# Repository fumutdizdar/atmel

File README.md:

# atmel
Atmel328P için temel board

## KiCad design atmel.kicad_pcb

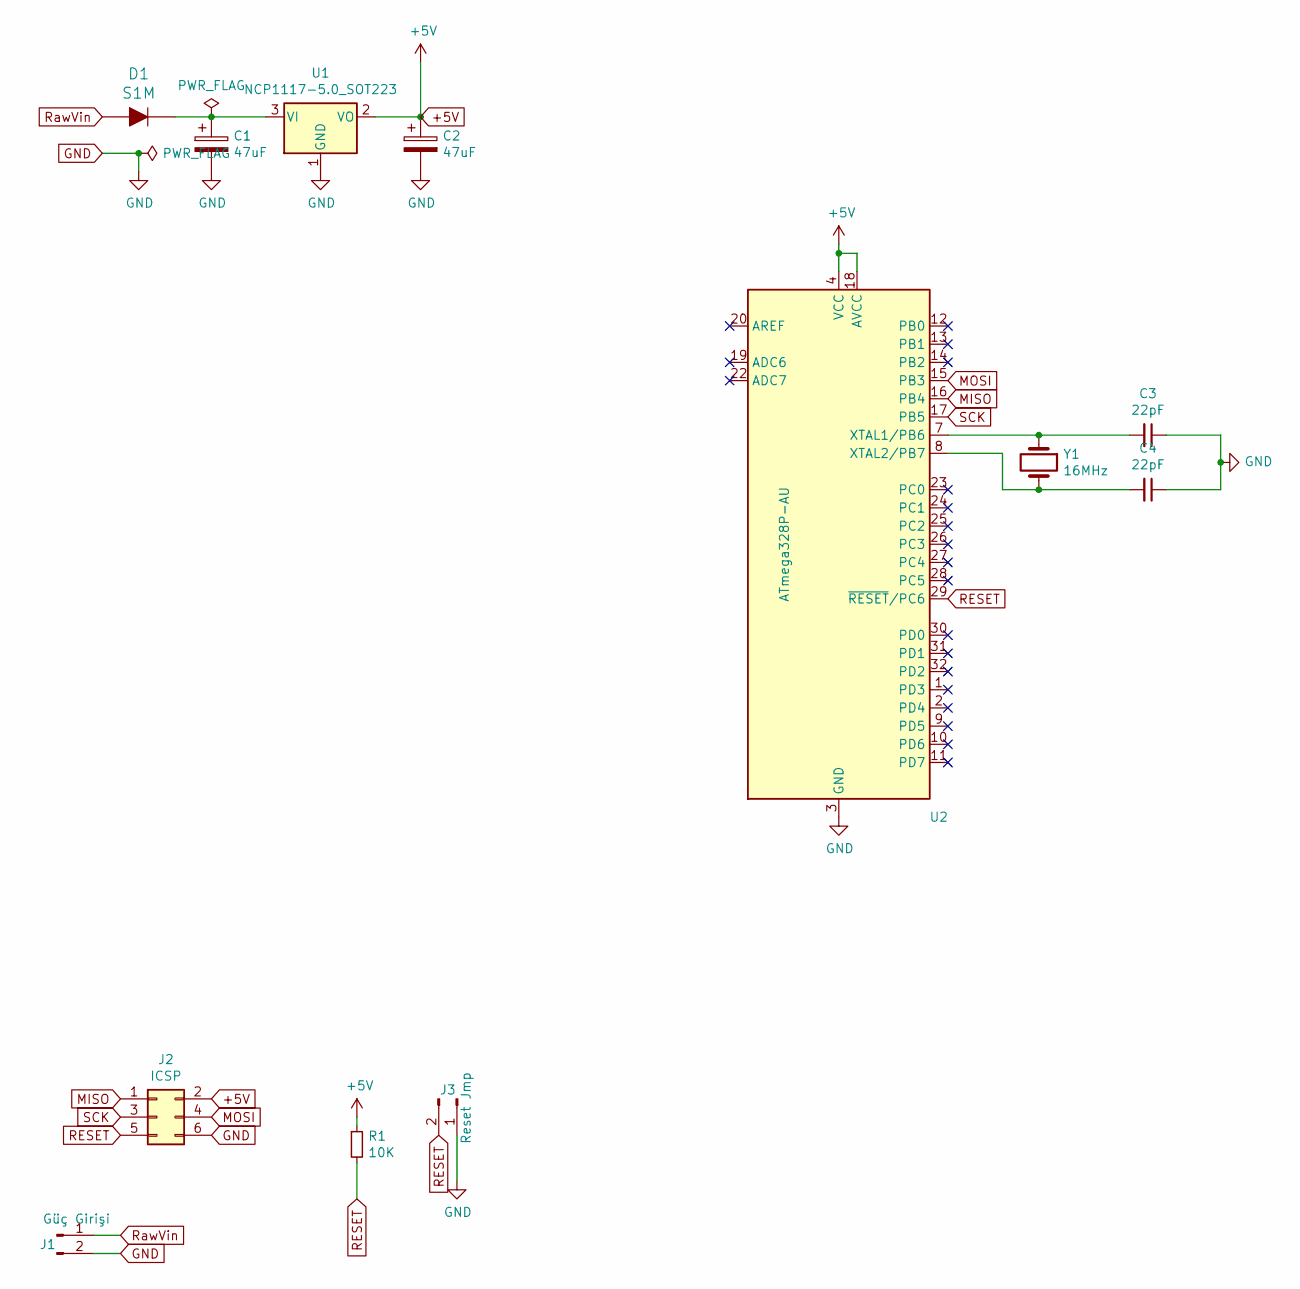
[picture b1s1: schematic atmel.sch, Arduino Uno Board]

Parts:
C1, C2: 47uF; CP_Elec_6.3x5.9
C3, C4: 22pF; C_0603_1608Metric_Pad1.05x0.95mm_HandSolder
D1: S1M; DO-214AC; MPN S1G; Digi-Key_PN S1GFSCT-ND
J1: Güç Girişi; PinHeader_1x02_P1.27mm_Vertical
J2: ICSP; PinHeader_2x03_P1.27mm_Vertical
J3: Reset Jmp; PinHeader_1x02_P1.27mm_Vertical
R1: 10K; R_0603_1608Metric_Pad1.05x0.95mm_HandSolder
U1: NCP1117-5.0_SOT223; SOT-223-3_TabPin2
U2: ATmega328P-AU; TQFP-32_7x7mm_P0.8mm
Y1: 16MHz; Crystal_SMD_0603-2Pin_6.0x3.5mm_HandSoldering

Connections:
+5V: C2.1, J2.2, R1.1, U1.2 (VO), U2.4 (VCC), U2.6 (VCC), U2.18 (AVCC)
GND: C1.2, C2.2, C3.1, C4.1, J1.2, J2.6, J3.1, U1.1 (GND), U2.3 (GND), U2.5 (GND), U2.21 (GND)
MISO: J2.1, U2.16 (PB4)
MOSI: J2.4, U2.15 (PB3)
unnamed: C1.1, D1.K, U1.3 (VI)
unnamed: C3.2, U2.7 (XTAL1/PB6), Y1.1
unnamed: C4.2, U2.8 (XTAL2/PB7), Y1.2
RESET: J2.5, J3.2, R1.2, U2.29 (~RESET~/PC6)
RawVin: D1.A, J1.1
SCK: J2.3, U2.17 (PB5)

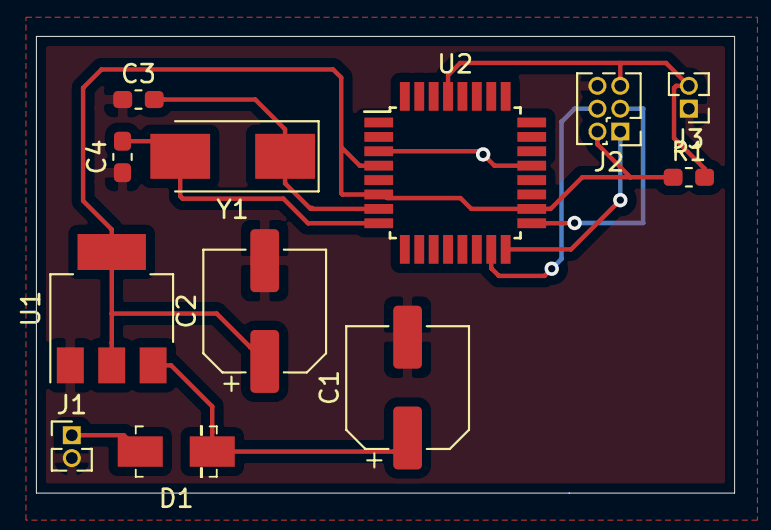
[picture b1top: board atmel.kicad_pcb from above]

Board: 2 copper layers, 38.8 x 25.4 mm, 12 parts (0 on the bottom side), 10 nets.

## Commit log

2020-03-21 21 Mart Ev
